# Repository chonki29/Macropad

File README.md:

# Custom Macropad

A custom 5-key macropad built around the Seeed XIAO RP2040.

## Features

- 5× Cherry MX-style switches
- EC11 rotary encoder for volume
- 0.91" 128×32 OLED
- Custom PCB
- Custom 3D-printed case
- QMK firmware
- USB-C

## PCB

Designed in KiCad.
## Schematic 

## Case

Designed in Fusion 360.

## Firmware

Built using QMK for the XIAO RP2040.

## Production

Production files are available in the `production` folder, including:

- `gerbers.zip`
- `Top.stl`
- `Bottom.stl`
- `Knob.stl`
- `firmware.uf2`

## Credits

Designed and built by **me (daksh agrawal)**  

thanks for checking out my project :)))

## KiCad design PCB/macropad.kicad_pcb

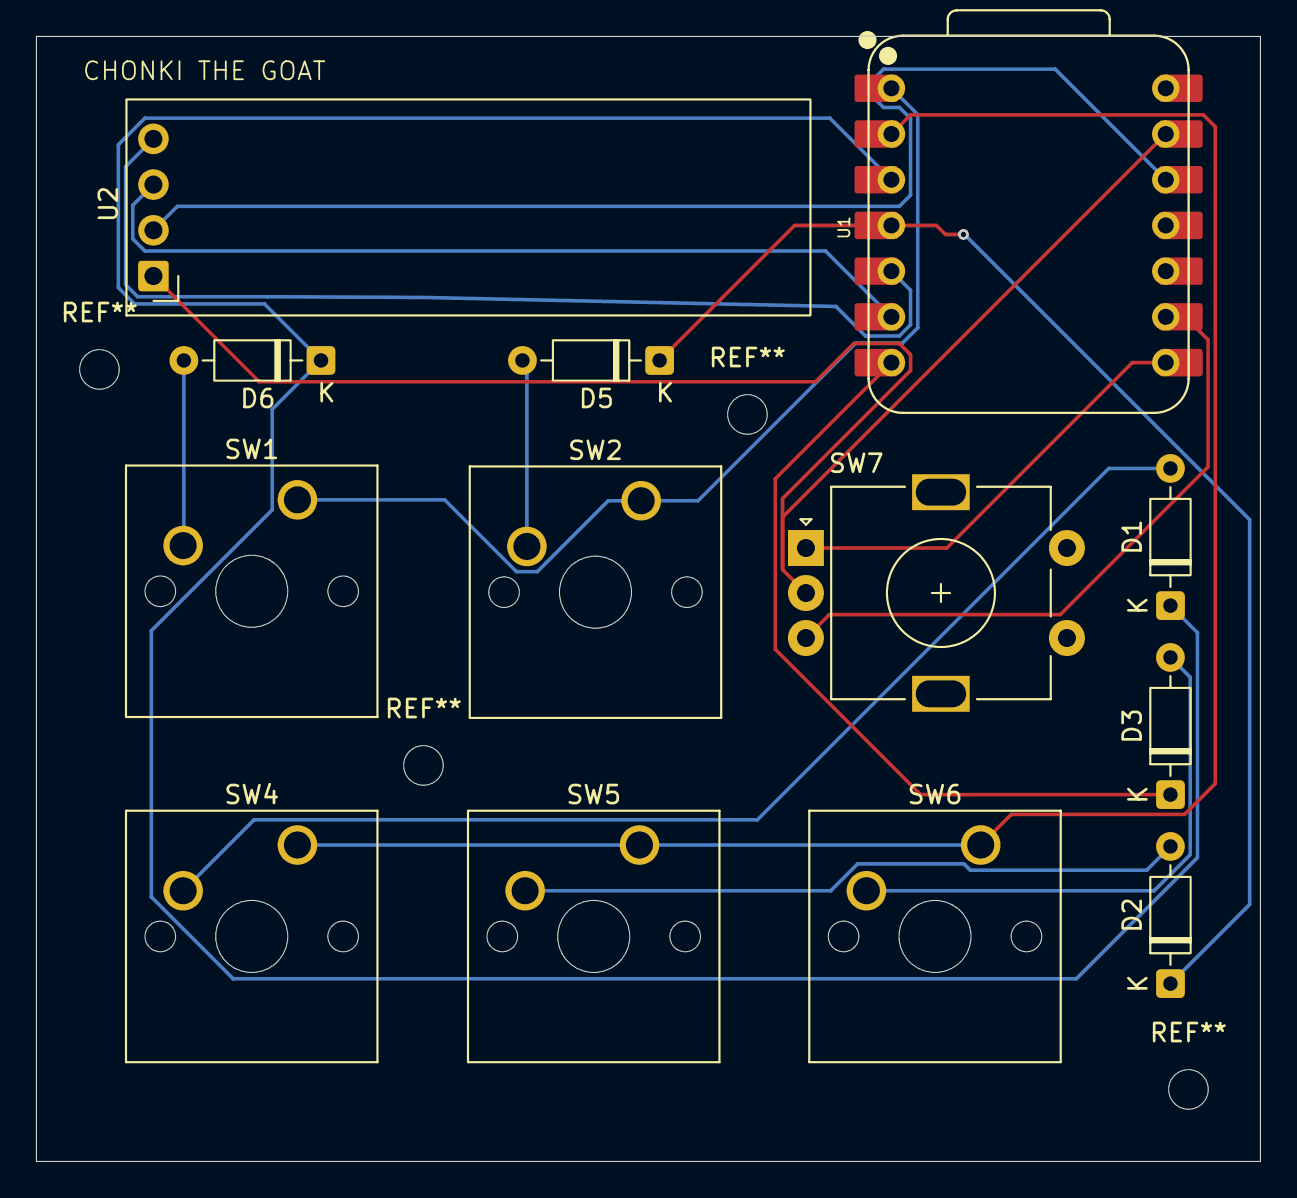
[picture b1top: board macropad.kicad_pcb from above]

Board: 2 copper layers, 68.0 x 62.5 mm, 13 parts (0 on the bottom side), 16 nets.

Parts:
D1, D2, D3, D5, D6: 1N4148; D_DO-35_SOD27_P7.62mm_Horizontal
SW1, SW2, SW4, SW5, SW6: SW_Push; SW_Cherry_MX_1.00u_PCB
SW7: RotaryEncoder_Switch; RotaryEncoder_Alps_EC11E-Switch_Vertical_H20mm
U1: MOUDLE-SEEEDUINO-XIAO; XIAO-RP2040-DIP
U2: ER_OLEDM0.91_1x-I2C

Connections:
/C1: D1.1 (K), D6.1 (K), U1.3 (PA10_A2_D2)
/C2: D2.1 (K), D5.1 (K), U1.4 (PA11_A3_D3)
/C3: D3.1 (K), U1.7 (PB08_A6_D6_TX)
/EC-A: SW7.A, U1.8 (PB09_A7_D7_RX)
/EC-B: SW7.B, U1.9 (PA7_A8_D8_SCK)
/GND: SW7.C, U1.13 (GND), U2.1 (GND)
/OLED VCC: U1.12 (3V3), U2.2 (VCC)
/R1: SW1.1, SW2.1, U1.1 (PA02_A0_D0)
/R2: SW4.1, SW5.1, SW6.1, U1.2 (PA4_A1_D1)
/SDA: U1.5 (PA8_A4_D4_SDA), U2.4 (SDA)
/SLC: U1.6 (PA9_A5_D5_SCL), U2.3 (SCL)
unnamed: D1.2 (A), SW4.2
unnamed: D2.2 (A), SW5.2
unnamed: D3.2 (A), SW6.2
unnamed: D5.2 (A), SW2.2
unnamed: D6.2 (A), SW1.2
